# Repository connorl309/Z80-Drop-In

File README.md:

# Z80-Drop-In
Relevant links and information:
- [Instruction Set](https://map.grauw.nl/resources/z80instr.php)
- [Z80 User Manual](https://www.zilog.com/docs/z80/um0080.pdf)
- [Master Reference Website](http://z80.info/)
- [Timing Quirks](https://floooh.github.io/2021/12/06/z80-instruction-timing.html#extra-clock-cycles)

## Summary
This is the Github repository for the senior design capstone project class at the University of Texas at Austin's ECE program (ECE 364/464). Our group is Industry Honors 01 (IH01), a Drop-in CPU Replacement for the Zilog Z80 processor, comprised of six members:

1. [Connor Leu](https://github.com/connorl309) - Team lead, organizer, maintainer, PCB design
2. [April Douglas](https://github.com/MaprilBear) - ALU RTL, processor design
3. [Gage Miller](https://github.com/millergage) - Register file RTL, processor design
4. [Luke Mason](https://github.com/Mega567835) - Control store, microsequencer, FSM design
5. [Nadia Houston](https://github.com/nadiahouston) - Control store, microsequencer, FSM design
6. [Gabriel Moore](https://github.com/K0-p) - Hardware testing, development boards

This project is considered an industry-honors project; as such, we are sponsored and primarily funded by an industry company, [Phoenix Semiconductor](https://www.phoenixsemicorp.com/).

The premise behind our drop-in replacement is to create a cycle-accurate processor core emulator on an FPGA. For our project, under company guidance, we are targeting the Spartan-7 XC7S15. The emulated processor core will sit on a supporting custom PCB, sized to the original form factor (approx. 17mm x 50mm) of the Zilog Z80. This PCB will then assume the position of a Z80 in any Z80 system, mimicking original processor behavior accurately.

The two major components of this project is the processor design and the hardware design. Our processor emulation core is split into datapath design and a control store/microcode FSM. The three major components of the datapath are the ALU, register file, and control logic. The control store and microcode represent our implementation of the original Z80's PLA for instruction decode and processor operation. Our RTL design decisions have been informed by over 40 years of processor execution behavior, the original user manual, and countless online documents written by reverse engineers and hobbyists. (see [Master Reference Website](http://z80.info/))

The hardware design is also split into two primary components: the devhat translation boards, used to level-shift our development boards 3.3V signals to the Z80 5V level and vice versa, and the System-in-Package board, which is the final goal of the project. The SiP board features the Spartan-7 FPGA, control hardware, QSPI flash memory, and other supporting circuitry in the size of the original Z80 package. Our hope is that this final board will be a true drop-in replacement for Z80 processors.

The SiP board can be found in [hardware/sip-board](hardware/sip-board/), and the level shifter board can be found in [hardware/level-shifter/](hardware/level-shifter/). Component files are kind of messy, but both Kicad Projects should all be using RELATIVE paths for custom symbols and footprints.

## Tools
Given the nature of an FPGA-based processor emulator, we opted to use as many industry-standard tools as possible. Our RTL is written in Verilog under the Vivado Design Suite, targeting a Spartan-7 **XC7S15** FPGA for final project completion. We are hoping to acquire physical testing equipment to validate circuit boards. Our hardware is designed using KiCad, as the University does not provide licenses for software such as Altium or Allegro.

## Building and Testing
Vivado's IP for FPGAs has lots of different blocks we can use. One such IP block is the [integrated logic analyzer (ILA)](https://www.xilinx.com/products/intellectual-property/ila.html). Instead of needing more PCBs or fancy test rigs, we can utilize the ILA directly on our development FPGA boards and dump waveforms right back out to the host PC and into the Vivado Waveform viewer. This is our primary method of testing and verification on the development boards (purchased from Numato - the Narvi S7). In addition to the ILA, our devboards also contain FTDI chips that let us communicate over serial to the host computer.
Our goal for devboard testing is to be able to execute any number of sample programs for the Z80, and verify that all control signals are accurate to both the M- and T-cycle level. This will likely take the form of short sample programs for all instructions, and then combined into larger test programs with more complex behavior whose validity will be examined on a results level, not a cycle level.

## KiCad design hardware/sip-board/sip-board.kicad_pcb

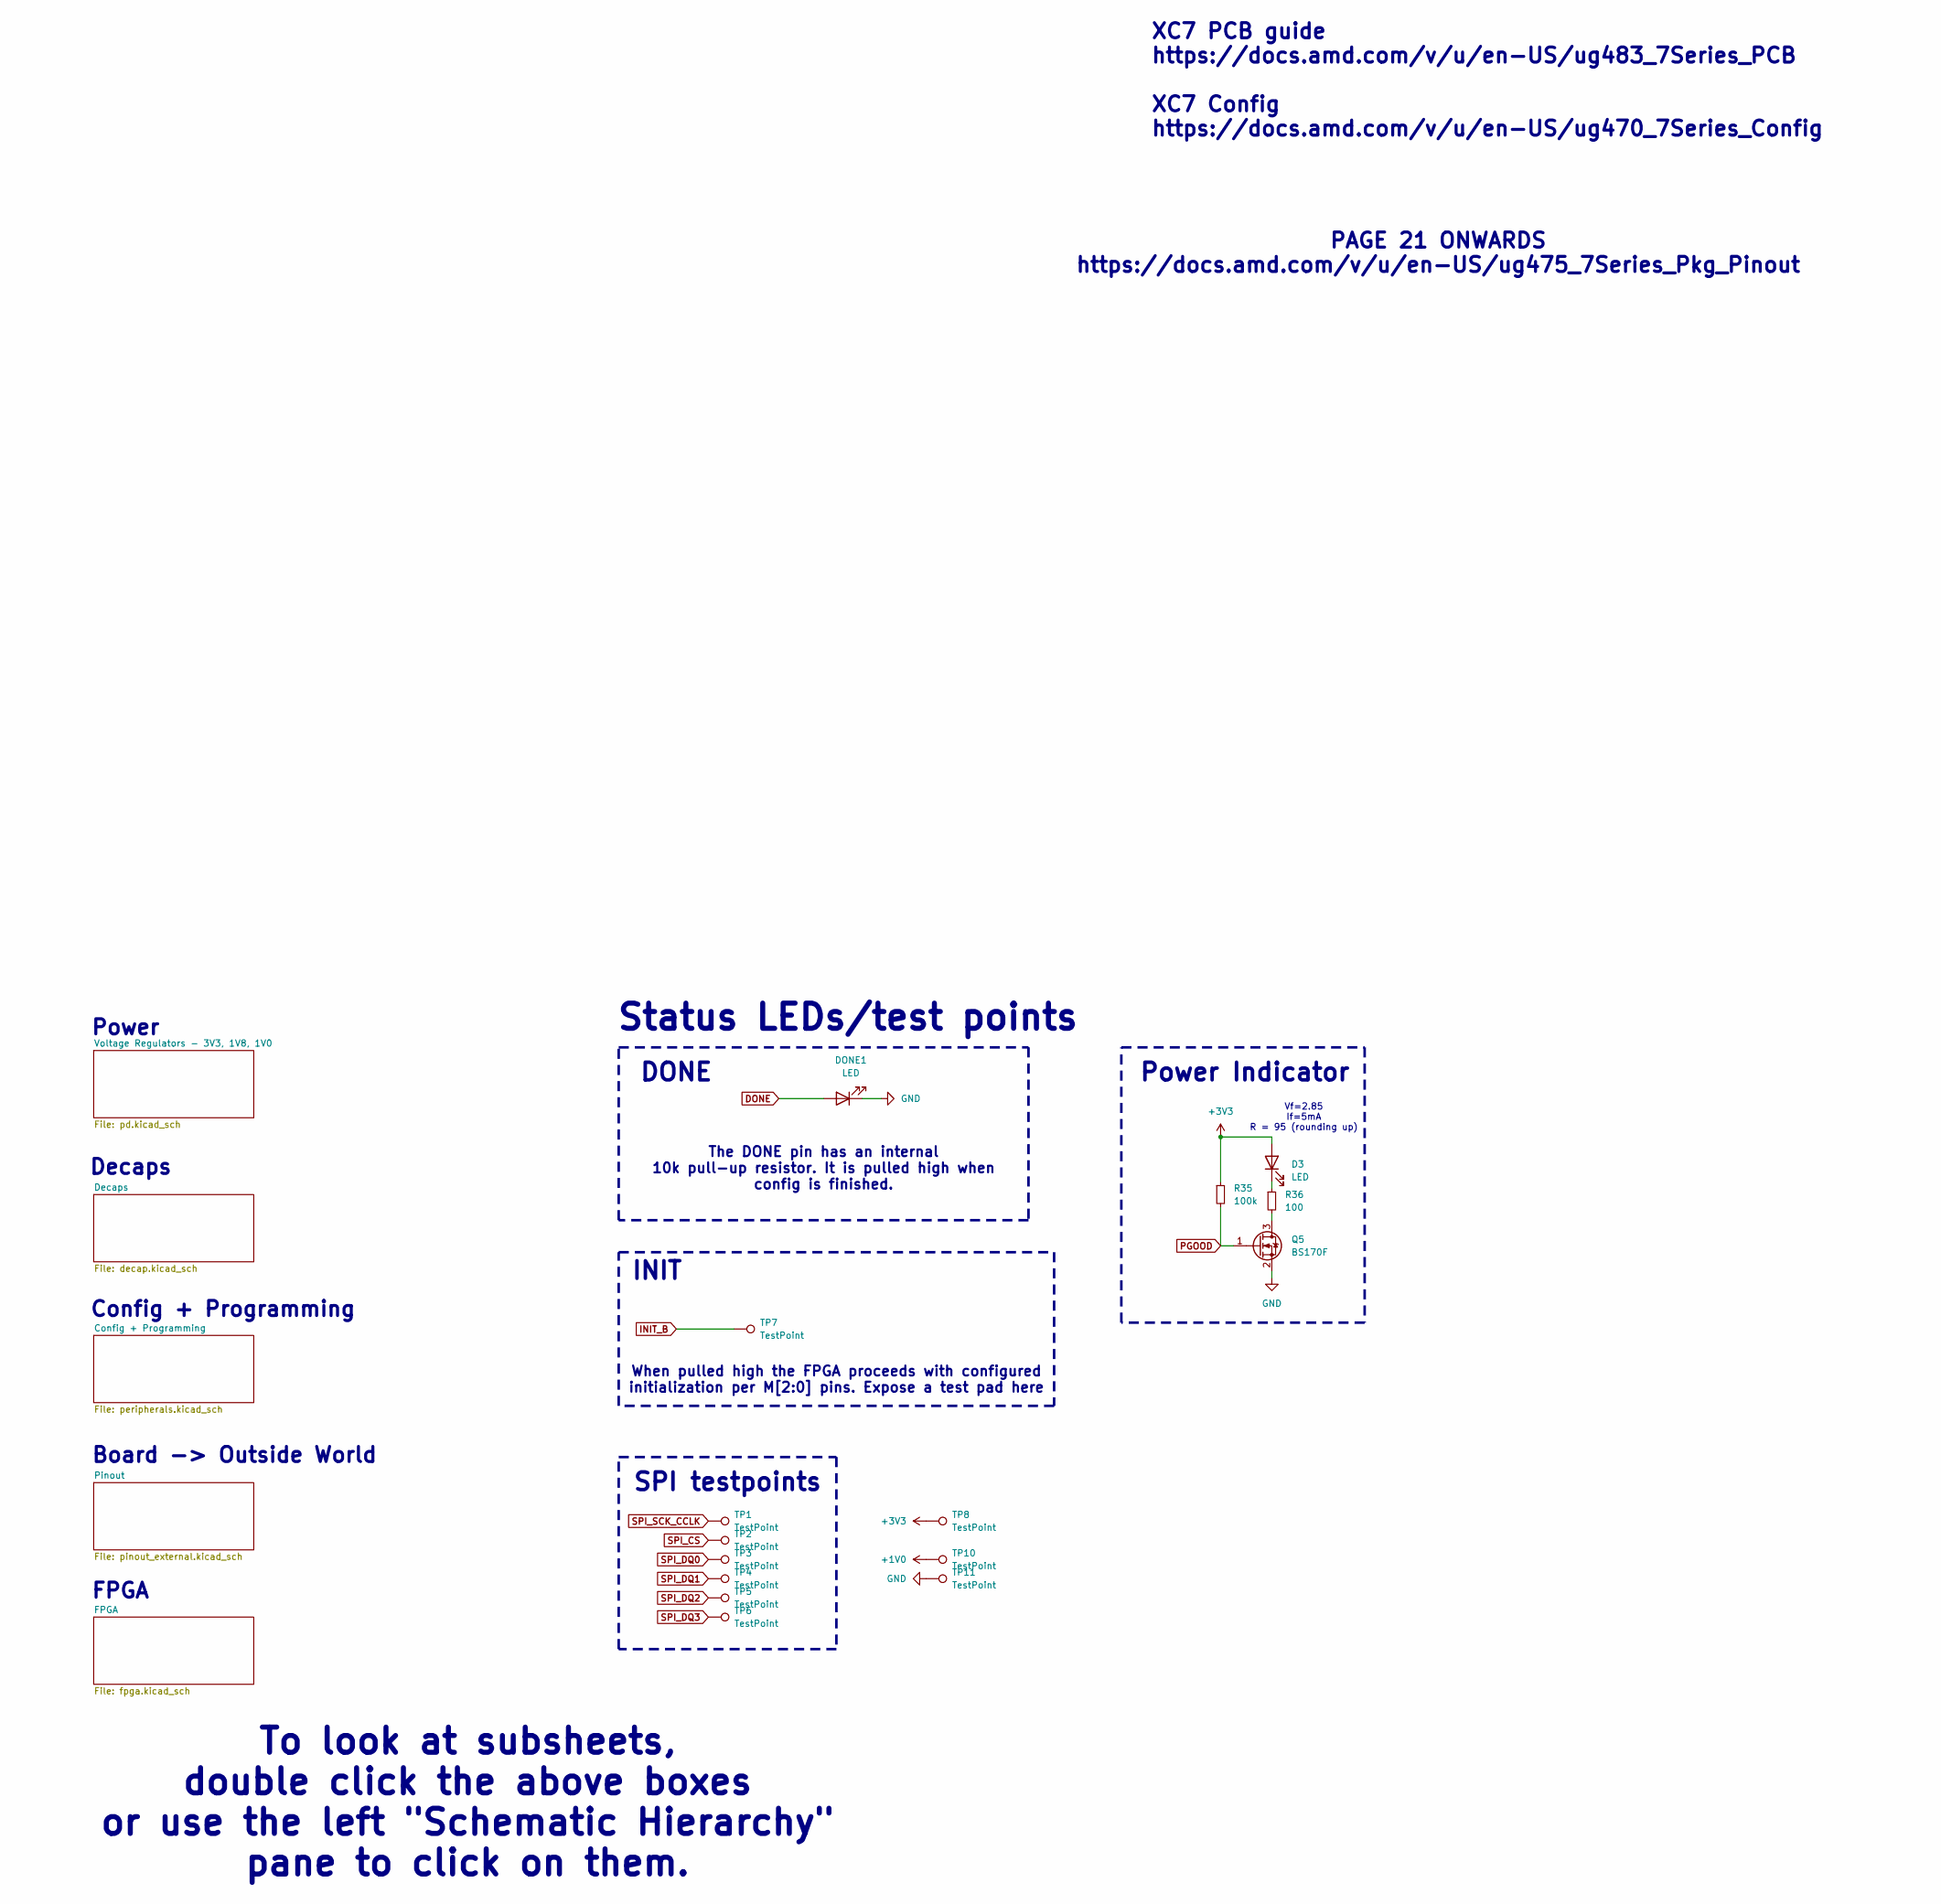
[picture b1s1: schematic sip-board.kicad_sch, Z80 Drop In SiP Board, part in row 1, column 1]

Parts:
D3: LED; LED_0402_1005Metric
DONE1: LED; LED_0402_1005Metric
Q5: BS170F; SOT-23
R35: 100k; R_0201_0603Metric
R36: 100; R_0201_0603Metric
TP1, TP2, TP3, TP4, TP5, TP6, TP7, TP8, TP10, TP11: TestPoint; TestPoint_Pad_1.0x1.0mm

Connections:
+1V0: TP10.1; also elsewhere on the board
+3V3: D3.2 (A), R35.1, TP8.1; also elsewhere on the board
DONE: DONE1.2 (A); also elsewhere on the board
GND: DONE1.1 (K), Q5.2 (S), TP11.1; also elsewhere on the board
INIT_B: TP7.1; also elsewhere on the board
unnamed: D3.1 (K), R36.1
unnamed: Q5.3 (D), R36.2
PGOOD: Q5.1 (G), R35.2; also elsewhere on the board
SPI_CS: TP2.1; also elsewhere on the board
SPI_DQ0: TP3.1; also elsewhere on the board
SPI_DQ1: TP4.1; also elsewhere on the board
SPI_DQ2: TP5.1; also elsewhere on the board
SPI_DQ3: TP6.1; also elsewhere on the board
SPI_SCK_CCLK: TP1.1; also elsewhere on the board

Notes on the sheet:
Power
Status LEDs/test points
FPGA
Decaps
XC7 PCB guide https://docs.amd.com/v/u/en-US/ug483_7Series_PCB XC7 Config https://docs.amd.com/v/u/en-US/ug470_7Series_Config
Board -> Outside World
Power Indicator
PAGE 21 ONWARDS https://docs.amd.com/v/u/en-US/ug475_7Series_Pkg_Pinout
INIT
Config + Programming
https://docs.amd.com/r/en-US/ug1099-bga-device-design-rules/Power-Delivery-to-the-FPGA
When pulled high the FPGA proceeds with configured initialization per M[2:0] pins. Expose a test pad here
DONE
The DONE pin has an internal 10k pull-up resistor. It is pulled high when config is finished.
SPI testpoints
To look at subsheets, double click the above boxes or use the left "Schematic Hierarchy" pane to click on them.
Vf=2.85 If=5mA R = 95 (rounding up)

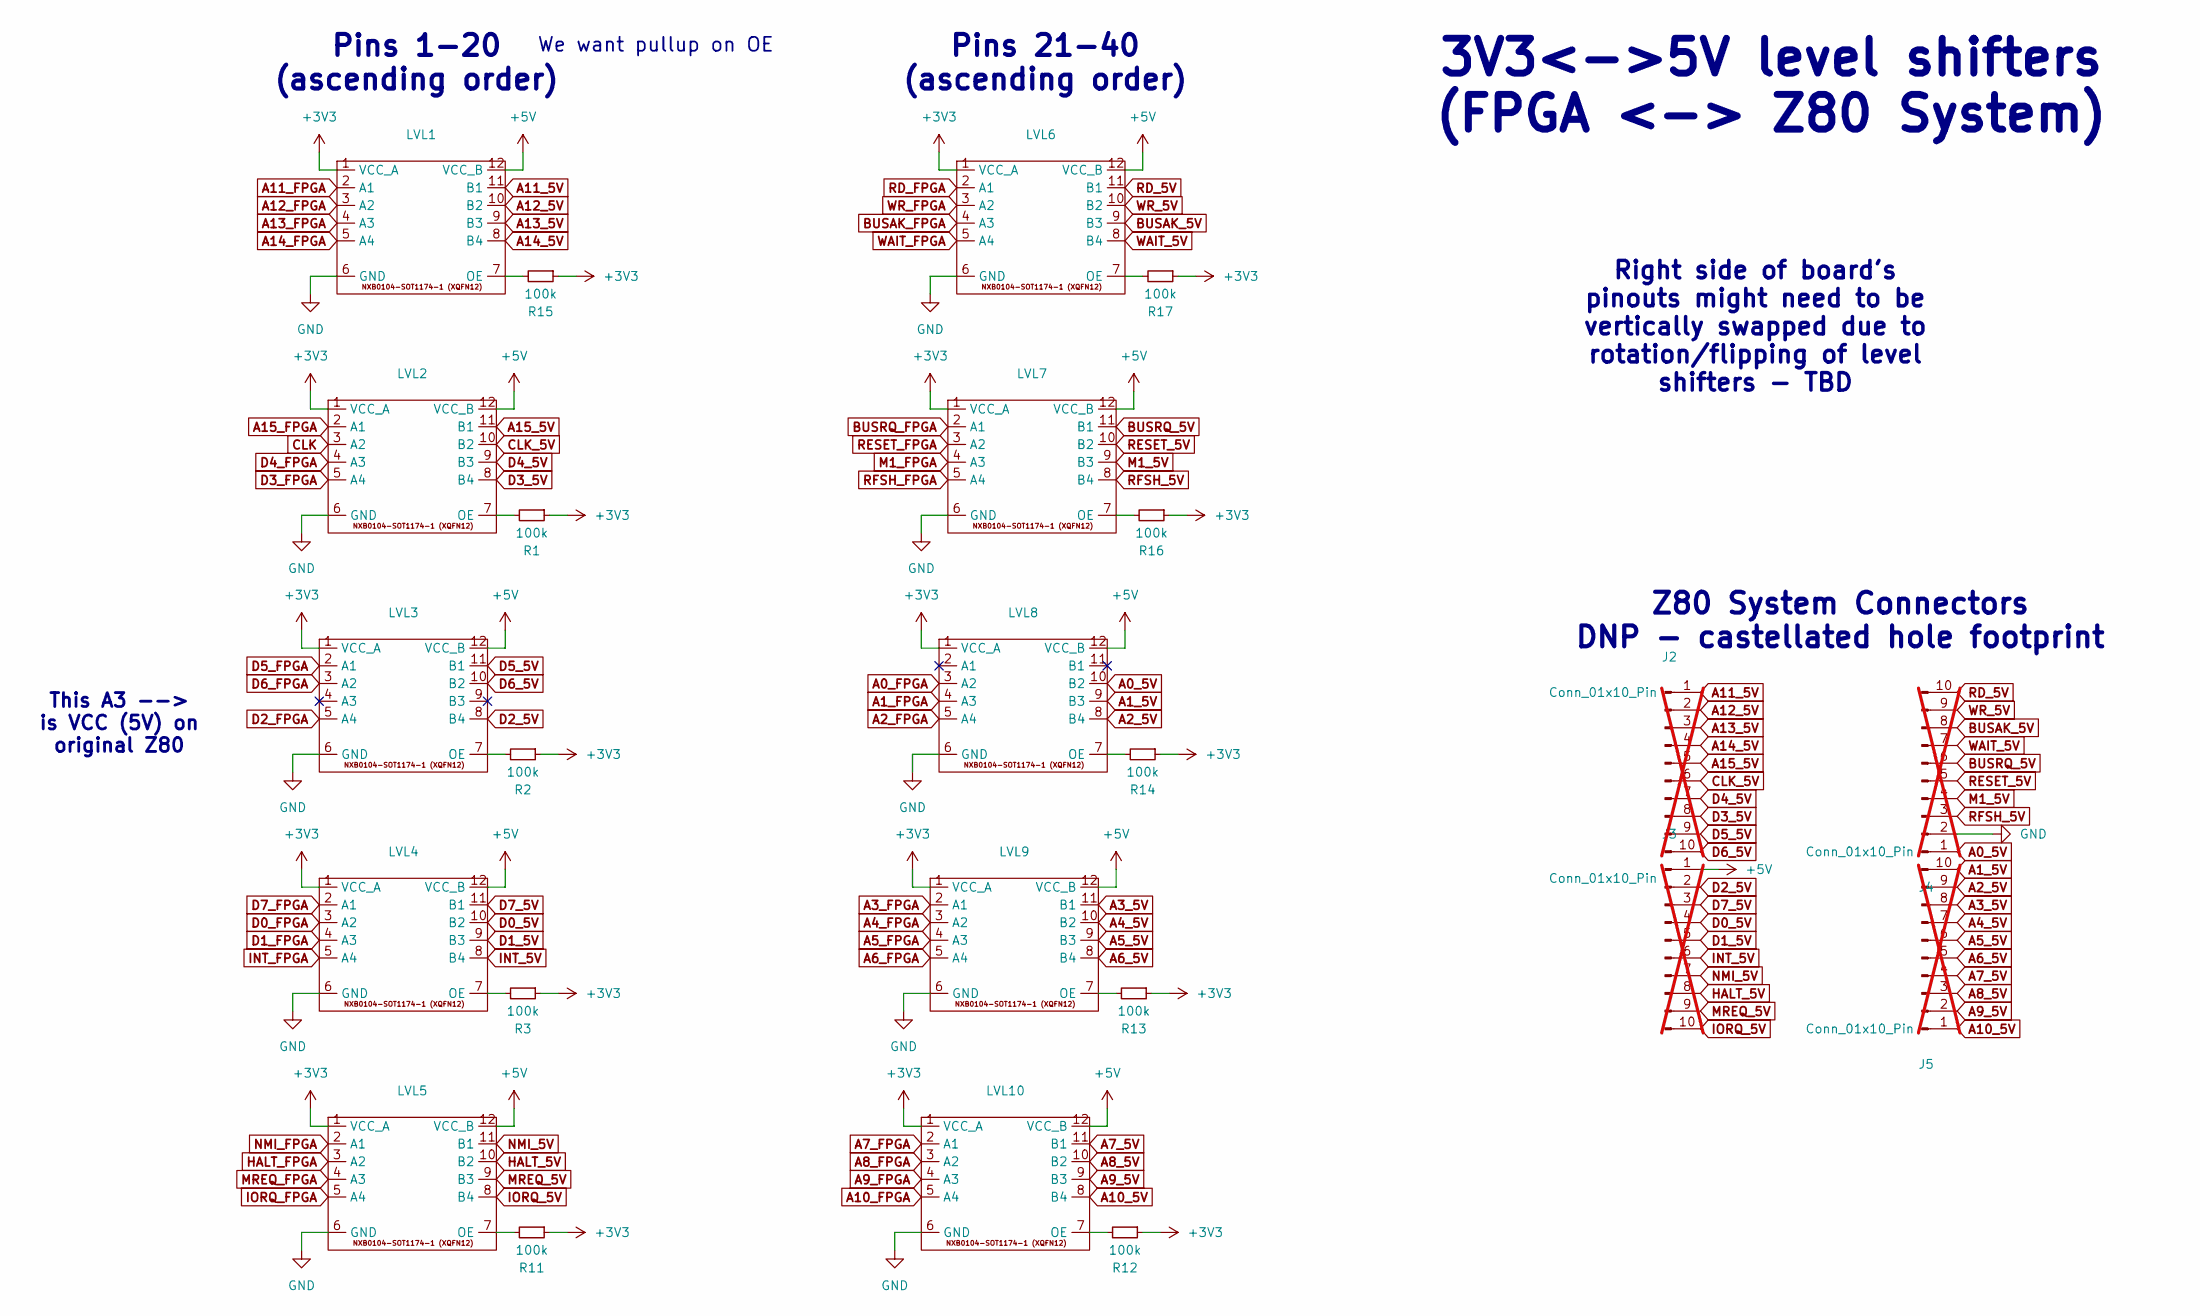
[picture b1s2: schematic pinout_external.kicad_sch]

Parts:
J2, J3, J4, J5: Conn_01x10_Pin; PinHeader_1x10_P2.54mm_Vertical; not fitted
LVL1, LVL2, LVL3, LVL4, LVL5, LVL6, LVL7, LVL8, LVL9, LVL10: NXB0104GU12X; MPN NXB0104GU12X
R1, R2, R3, R11, R12, R13, R14, R15, R16, R17: 100k; R_0201_0603Metric

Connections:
+3V3: LVL1.1 (VCC_A), LVL2.1 (VCC_A), LVL3.1 (VCC_A), LVL4.1 (VCC_A), LVL5.1 (VCC_A), LVL6.1 (VCC_A), LVL7.1 (VCC_A), LVL8.1 (VCC_A), LVL9.1 (VCC_A), LVL10.1 (VCC_A), R1.1, R2.1, R3.1, R11.1, R12.1, R13.1, R14.1, R15.1, R16.1, R17.1; also elsewhere on the board
+5V: J3.1, LVL1.12 (VCC_B), LVL2.12 (VCC_B), LVL3.12 (VCC_B), LVL4.12 (VCC_B), LVL5.12 (VCC_B), LVL6.12 (VCC_B), LVL7.12 (VCC_B), LVL8.12 (VCC_B), LVL9.12 (VCC_B), LVL10.12 (VCC_B); also elsewhere on the board
A0_5V: J4.1, LVL8.10 (B2)
A0_FPGA: LVL8.3 (A2); also elsewhere on the board
A1_5V: J5.10, LVL8.9 (B3)
A1_FPGA: LVL8.4 (A3); also elsewhere on the board
A2_5V: J5.9, LVL8.8 (B4)
A2_FPGA: LVL8.5 (A4); also elsewhere on the board
A3_5V: J5.8, LVL9.11 (B1)
A3_FPGA: LVL9.2 (A1); also elsewhere on the board
A4_5V: J5.7, LVL9.10 (B2)
A4_FPGA: LVL9.3 (A2); also elsewhere on the board
A5_5V: J5.6, LVL9.9 (B3)
A5_FPGA: LVL9.4 (A3); also elsewhere on the board
A6_5V: J5.5, LVL9.8 (B4)
A6_FPGA: LVL9.5 (A4); also elsewhere on the board
A7_5V: J5.4, LVL10.11 (B1)
A7_FPGA: LVL10.2 (A1); also elsewhere on the board
A8_5V: J5.3, LVL10.10 (B2)
A8_FPGA: LVL10.3 (A2); also elsewhere on the board
A9_5V: J5.2, LVL10.9 (B3)
A9_FPGA: LVL10.4 (A3); also elsewhere on the board
A10_5V: J5.1, LVL10.8 (B4)
A10_FPGA: LVL10.5 (A4); also elsewhere on the board
A11_5V: J2.1, LVL1.11 (B1)
A11_FPGA: LVL1.2 (A1); also elsewhere on the board
A12_5V: J2.2, LVL1.10 (B2)
A12_FPGA: LVL1.3 (A2); also elsewhere on the board
A13_5V: J2.3, LVL1.9 (B3)
A13_FPGA: LVL1.4 (A3); also elsewhere on the board
A14_5V: J2.4, LVL1.8 (B4)
A14_FPGA: LVL1.5 (A4); also elsewhere on the board
A15_5V: J2.5, LVL2.11 (B1)
A15_FPGA: LVL2.2 (A1); also elsewhere on the board
BUSAK_5V: J4.8, LVL6.9 (B3)
BUSAK_FPGA: LVL6.4 (A3); also elsewhere on the board
BUSRQ_5V: J4.6, LVL7.11 (B1)
BUSRQ_FPGA: LVL7.2 (A1); also elsewhere on the board
CLK: LVL2.3 (A2); also elsewhere on the board
CLK_5V: J2.6, LVL2.10 (B2)
D0_5V: J3.4, LVL4.10 (B2)
D0_FPGA: LVL4.3 (A2); also elsewhere on the board
D1_5V: J3.5, LVL4.9 (B3)
D1_FPGA: LVL4.4 (A3); also elsewhere on the board
D2_5V: J3.2, LVL3.8 (B4)
D2_FPGA: LVL3.5 (A4); also elsewhere on the board
D3_5V: J2.8, LVL2.8 (B4)
D3_FPGA: LVL2.5 (A4); also elsewhere on the board
D4_5V: J2.7, LVL2.9 (B3)
D4_FPGA: LVL2.4 (A3); also elsewhere on the board
D5_5V: J2.9, LVL3.11 (B1)
D5_FPGA: LVL3.2 (A1); also elsewhere on the board
D6_5V: J2.10, LVL3.10 (B2)
D6_FPGA: LVL3.3 (A2); also elsewhere on the board
D7_5V: J3.3, LVL4.11 (B1)
D7_FPGA: LVL4.2 (A1); also elsewhere on the board
GND: J4.2, LVL1.6 (GND), LVL2.6 (GND), LVL3.6 (GND), LVL4.6 (GND), LVL5.6 (GND), LVL6.6 (GND), LVL7.6 (GND), LVL8.6 (GND), LVL9.6 (GND), LVL10.6 (GND); also elsewhere on the board
HALT_5V: J3.8, LVL5.10 (B2)
HALT_FPGA: LVL5.3 (A2); also elsewhere on the board
INT_5V: J3.6, LVL4.8 (B4)
INT_FPGA: LVL4.5 (A4); also elsewhere on the board
IORQ_5V: J3.10, LVL5.8 (B4)
IORQ_FPGA: LVL5.5 (A4); also elsewhere on the board
M1_5V: J4.4, LVL7.9 (B3)
M1_FPGA: LVL7.4 (A3); also elsewhere on the board
MREQ_5V: J3.9, LVL5.9 (B3)
MREQ_FPGA: LVL5.4 (A3); also elsewhere on the board
NMI_5V: J3.7, LVL5.11 (B1)
NMI_FPGA: LVL5.2 (A1); also elsewhere on the board
unnamed: LVL1.7 (OE), R15.2
unnamed: LVL2.7 (OE), R1.2
unnamed: LVL3.7 (OE), R2.2
unnamed: LVL4.7 (OE), R3.2
unnamed: LVL5.7 (OE), R11.2
unnamed: LVL6.7 (OE), R17.2
unnamed: LVL7.7 (OE), R16.2
unnamed: LVL8.7 (OE), R14.2
unnamed: LVL9.7 (OE), R13.2
unnamed: LVL10.7 (OE), R12.2
RD_5V: J4.10, LVL6.11 (B1)
RD_FPGA: LVL6.2 (A1); also elsewhere on the board
RESET_5V: J4.5, LVL7.10 (B2)
RESET_FPGA: LVL7.3 (A2); also elsewhere on the board
RFSH_5V: J4.3, LVL7.8 (B4)
RFSH_FPGA: LVL7.5 (A4); also elsewhere on the board
WAIT_5V: J4.7, LVL6.8 (B4)
WAIT_FPGA: LVL6.5 (A4); also elsewhere on the board
WR_5V: J4.9, LVL6.10 (B2)
WR_FPGA: LVL6.3 (A2); also elsewhere on the board

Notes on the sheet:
3V3<->5V level shifters (FPGA <-> Z80 System)
Z80 System Connectors DNP - castellated hole footprint
This A3 --> is VCC (5V) on original Z80
We want pullup on OE
Right side of board's pinouts might need to be vertically swapped due to rotation/flipping of level shifters - TBD
Pins 21-40 (ascending order)
Pins 1-20 (ascending order)

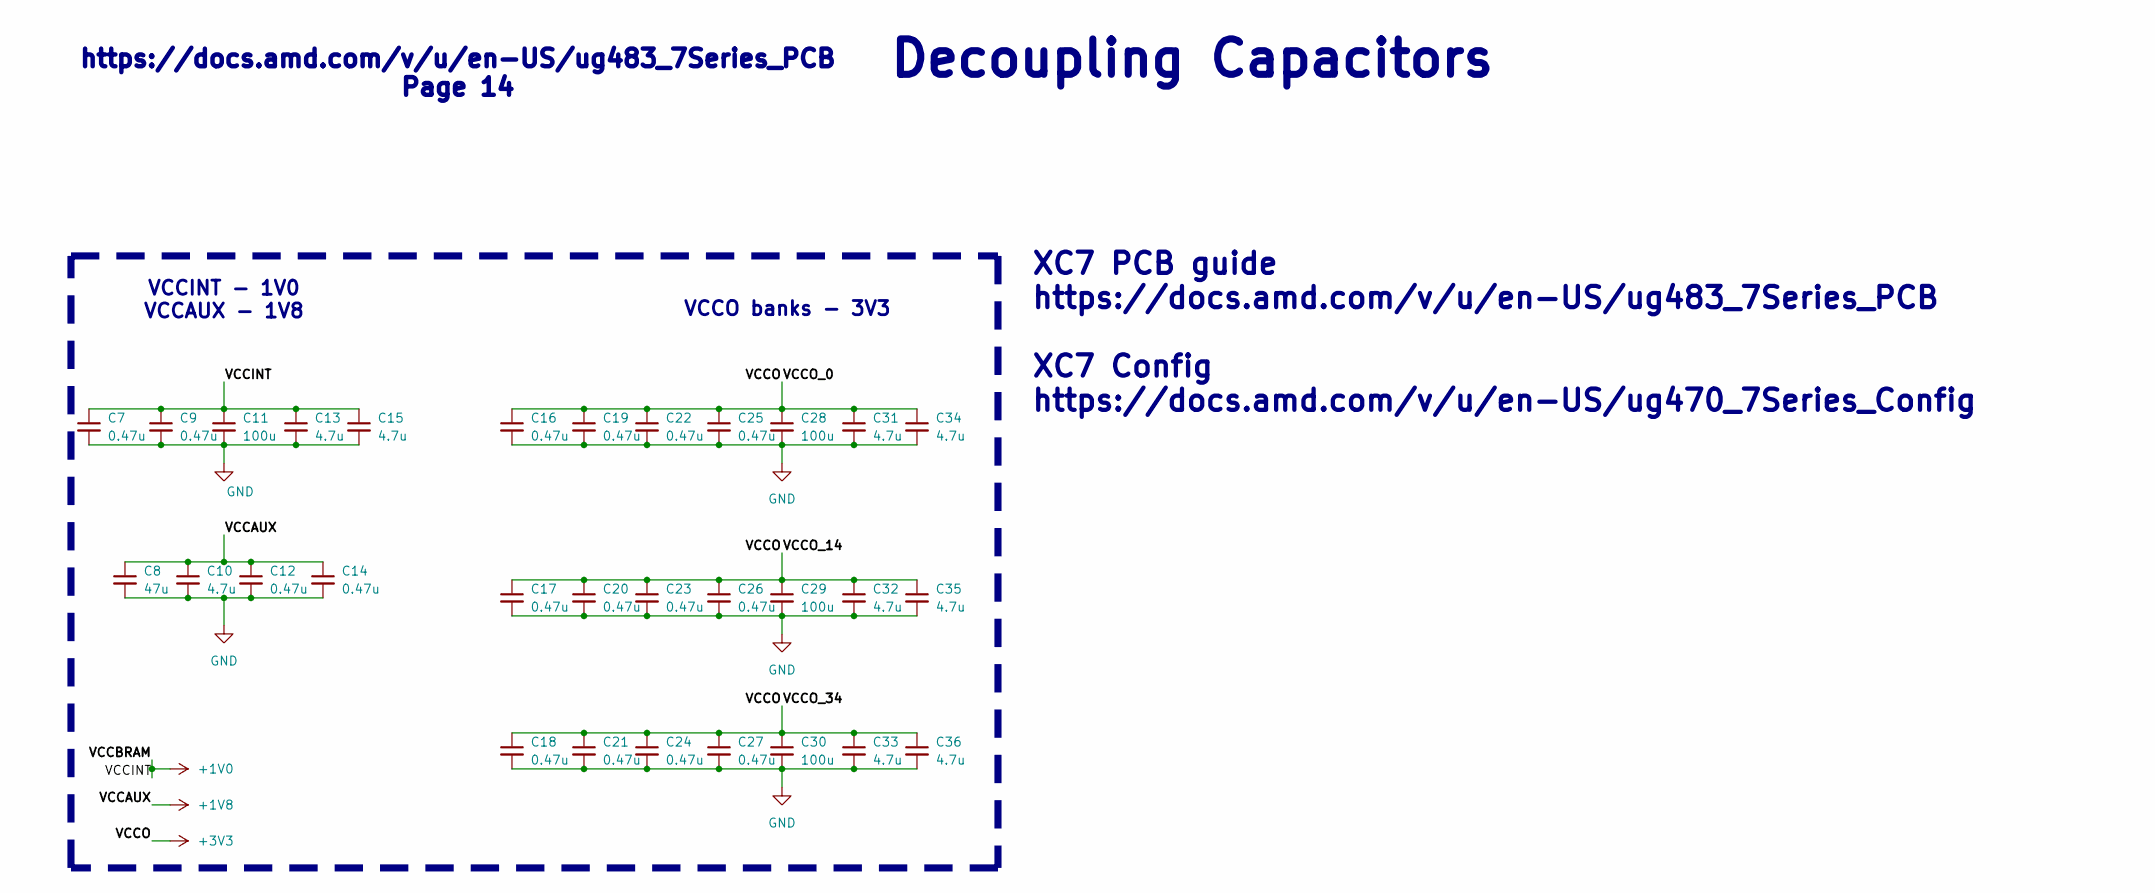
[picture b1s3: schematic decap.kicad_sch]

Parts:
C7, C9, C12, C14, C16, C17, C18, C19, C20, C21, C22, C23, C24, C25, C26, C27: 0.47u; C_0201_0603Metric
C8: 47u; C_0603_1608Metric
C10, C13, C15, C31, C32, C33, C34, C35, C36: 4.7u; C_0402_1005Metric
C11, C28, C29, C30: 100u; C_0603_1608Metric

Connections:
+1V0: C7.1, C9.1, C11.1, C13.1, C15.1; also elsewhere on the board
+1V8: C8.1, C10.1, C12.1, C14.1; also elsewhere on the board
+3V3: C16.1, C17.1, C18.1, C19.1, C20.1, C21.1, C22.1, C23.1, C24.1, C25.1, C26.1, C27.1, C28.1, C29.1, C30.1, C31.1, C32.1, C33.1, C34.1, C35.1, C36.1; also elsewhere on the board
GND: C7.2, C8.2, C9.2, C10.2, C11.2, C12.2, C13.2, C14.2, C15.2, C16.2, C17.2, C18.2, C19.2, C20.2, C21.2, C22.2, C23.2, C24.2, C25.2, C26.2, C27.2, C28.2, C29.2, C30.2, C31.2, C32.2, C33.2, C34.2, C35.2, C36.2; also elsewhere on the board

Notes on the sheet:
Decoupling Capacitors
XC7 PCB guide https://docs.amd.com/v/u/en-US/ug483_7Series_PCB XC7 Config https://docs.amd.com/v/u/en-US/ug470_7Series_Config
VCCO banks - 3V3
https://docs.amd.com/v/u/en-US/ug483_7Series_PCB Page 14
VCCINT - 1V0 VCCAUX - 1V8

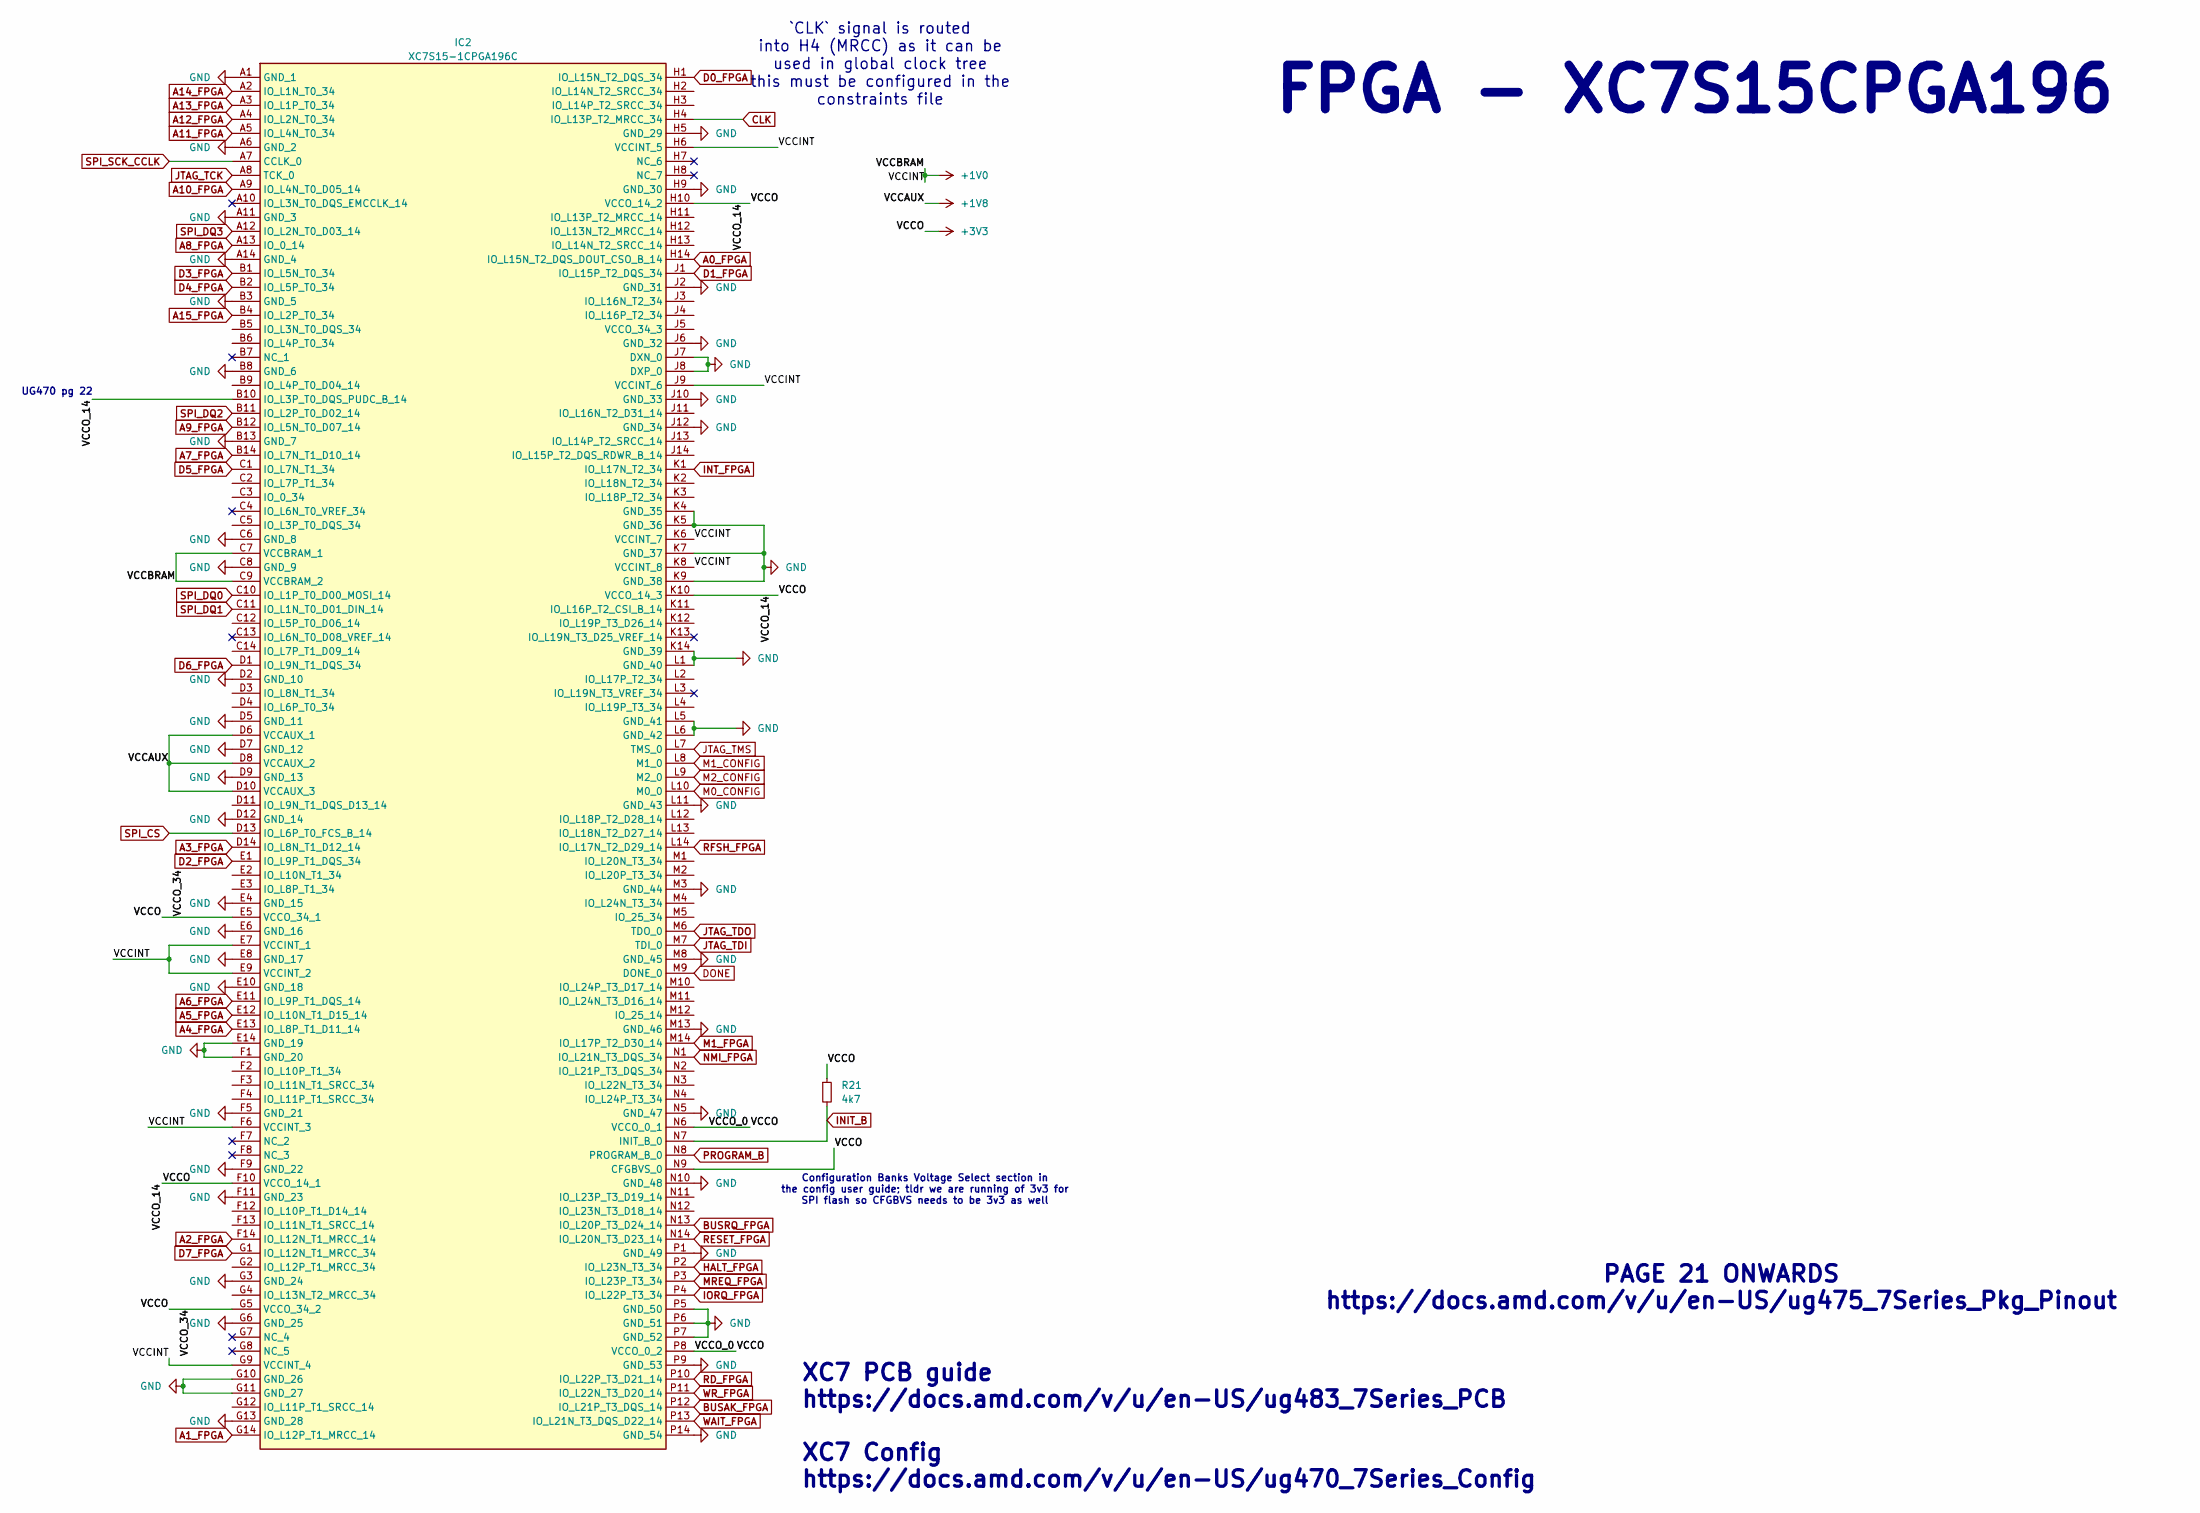
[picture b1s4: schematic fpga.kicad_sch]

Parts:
IC2: XC7S15-1CPGA196C; BGA196C50P14X14_800X800X110; Mouser Part Number 217-XC7S15-1CPGA196C
R21: 4k7; R_0201_0603Metric

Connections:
+1V0: IC2.C7 (VCCBRAM_1), IC2.C9 (VCCBRAM_2), IC2.E7 (VCCINT_1), IC2.E9 (VCCINT_2), IC2.F6 (VCCINT_3), IC2.G9 (VCCINT_4), IC2.H6 (VCCINT_5), IC2.J9 (VCCINT_6), IC2.K6 (VCCINT_7), IC2.K8 (VCCINT_8); also elsewhere on the board
+1V8: IC2.D6 (VCCAUX_1), IC2.D8 (VCCAUX_2), IC2.D10 (VCCAUX_3); also elsewhere on the board
+3V3: IC2.B10 (IO_L3P_T0_DQS_PUDC_B_14), IC2.E5 (VCCO_34_1), IC2.F10 (VCCO_14_1), IC2.G5 (VCCO_34_2), IC2.H10 (VCCO_14_2), IC2.K10 (VCCO_14_3), IC2.N6 (VCCO_0_1), IC2.N9 (CFGBVS_0), IC2.P8 (VCCO_0_2), R21.1; also elsewhere on the board
A0_FPGA: IC2.H14 (IO_L15N_T2_DQS_DOUT_CSO_B_14); also elsewhere on the board
A1_FPGA: IC2.G14 (IO_L12P_T1_MRCC_14); also elsewhere on the board
A2_FPGA: IC2.F14 (IO_L12N_T1_MRCC_14); also elsewhere on the board
A3_FPGA: IC2.D14 (IO_L8N_T1_D12_14); also elsewhere on the board
A4_FPGA: IC2.E13 (IO_L8P_T1_D11_14); also elsewhere on the board
A5_FPGA: IC2.E12 (IO_L10N_T1_D15_14); also elsewhere on the board
A6_FPGA: IC2.E11 (IO_L9P_T1_DQS_14); also elsewhere on the board
A7_FPGA: IC2.B14 (IO_L7N_T1_D10_14); also elsewhere on the board
A8_FPGA: IC2.A13 (IO_0_14); also elsewhere on the board
A9_FPGA: IC2.B12 (IO_L5N_T0_D07_14); also elsewhere on the board
A10_FPGA: IC2.A9 (IO_L4N_T0_D05_14); also elsewhere on the board
A11_FPGA: IC2.A5 (IO_L4N_T0_34); also elsewhere on the board
A12_FPGA: IC2.A4 (IO_L2N_T0_34); also elsewhere on the board
A13_FPGA: IC2.A3 (IO_L1P_T0_34); also elsewhere on the board
A14_FPGA: IC2.A2 (IO_L1N_T0_34); also elsewhere on the board
A15_FPGA: IC2.B4 (IO_L2P_T0_34); also elsewhere on the board
BUSAK_FPGA: IC2.P12 (IO_L21P_T3_DQS_14); also elsewhere on the board
BUSRQ_FPGA: IC2.N13 (IO_L20P_T3_D24_14); also elsewhere on the board
CLK: IC2.H4 (IO_L13P_T2_MRCC_34); also elsewhere on the board
D0_FPGA: IC2.H1 (IO_L15N_T2_DQS_34); also elsewhere on the board
D1_FPGA: IC2.J1 (IO_L15P_T2_DQS_34); also elsewhere on the board
D2_FPGA: IC2.E1 (IO_L9P_T1_DQS_34); also elsewhere on the board
D3_FPGA: IC2.B1 (IO_L5N_T0_34); also elsewhere on the board
D4_FPGA: IC2.B2 (IO_L5P_T0_34); also elsewhere on the board
D5_FPGA: IC2.C1 (IO_L7N_T1_34); also elsewhere on the board
D6_FPGA: IC2.D1 (IO_L9N_T1_DQS_34); also elsewhere on the board
D7_FPGA: IC2.G1 (IO_L12N_T1_MRCC_34); also elsewhere on the board
DONE: IC2.M9 (DONE_0); also elsewhere on the board
GND: IC2.A1 (GND_1), IC2.A6 (GND_2), IC2.A11 (GND_3), IC2.A14 (GND_4), IC2.B3 (GND_5), IC2.B8 (GND_6), IC2.B13 (GND_7), IC2.C6 (GND_8), IC2.C8 (GND_9), IC2.D2 (GND_10), IC2.D5 (GND_11), IC2.D7 (GND_12), IC2.D9 (GND_13), IC2.D12 (GND_14), IC2.E4 (GND_15), IC2.E6 (GND_16), IC2.E8 (GND_17), IC2.E10 (GND_18), IC2.E14 (GND_19), IC2.F1 (GND_20), IC2.F5 (GND_21), IC2.F9 (GND_22), IC2.F11 (GND_23), IC2.G3 (GND_24), IC2.G6 (GND_25), IC2.G10 (GND_26), IC2.G11 (GND_27), IC2.G13 (GND_28), IC2.H5 (GND_29), IC2.H9 (GND_30), IC2.J2 (GND_31), IC2.J6 (GND_32), IC2.J7 (DXN_0), IC2.J8 (DXP_0), IC2.J10 (GND_33), IC2.J12 (GND_34), IC2.K4 (GND_35), IC2.K5 (GND_36), IC2.K7 (GND_37), IC2.K9 (GND_38), IC2.K14 (GND_39), IC2.L1 (GND_40), IC2.L5 (GND_41), IC2.L6 (GND_42), IC2.L11 (GND_43), IC2.M3 (GND_44), IC2.M8 (GND_45), IC2.M13 (GND_46), IC2.N5 (GND_47), IC2.N10 (GND_48), IC2.P1 (GND_49), IC2.P5 (GND_50), IC2.P6 (GND_51), IC2.P7 (GND_52), IC2.P9 (GND_53), IC2.P14 (GND_54); also elsewhere on the board
HALT_FPGA: IC2.P2 (IO_L23N_T3_34); also elsewhere on the board
INIT_B: IC2.N7 (INIT_B_0), R21.2; also elsewhere on the board
INT_FPGA: IC2.K1 (IO_L17N_T2_34); also elsewhere on the board
IORQ_FPGA: IC2.P4 (IO_L22P_T3_34); also elsewhere on the board
JTAG_TCK: IC2.A8 (TCK_0); also elsewhere on the board
JTAG_TDI: IC2.M7 (TDI_0); also elsewhere on the board
JTAG_TDO: IC2.M6 (TDO_0); also elsewhere on the board
JTAG_TMS: IC2.L7 (TMS_0); also elsewhere on the board
M0_CONFIG: IC2.L10 (M0_0); also elsewhere on the board
M1_CONFIG: IC2.L8 (M1_0); also elsewhere on the board
M1_FPGA: IC2.M14 (IO_L17P_T2_D30_14); also elsewhere on the board
M2_CONFIG: IC2.L9 (M2_0); also elsewhere on the board
MREQ_FPGA: IC2.P3 (IO_L23P_T3_34); also elsewhere on the board
NMI_FPGA: IC2.N1 (IO_L21N_T3_DQS_34); also elsewhere on the board
PROGRAM_B: IC2.N8 (PROGRAM_B_0); also elsewhere on the board
RD_FPGA: IC2.P10 (IO_L22P_T3_D21_14); also elsewhere on the board
RESET_FPGA: IC2.N14 (IO_L20N_T3_D23_14); also elsewhere on the board
RFSH_FPGA: IC2.L14 (IO_L17N_T2_D29_14); also elsewhere on the board
SPI_CS: IC2.D13 (IO_L6P_T0_FCS_B_14); also elsewhere on the board
SPI_DQ0: IC2.C10 (IO_L1P_T0_D00_MOSI_14); also elsewhere on the board
SPI_DQ1: IC2.C11 (IO_L1N_T0_D01_DIN_14); also elsewhere on the board
SPI_DQ2: IC2.B11 (IO_L2P_T0_D02_14); also elsewhere on the board
SPI_DQ3: IC2.A12 (IO_L2N_T0_D03_14); also elsewhere on the board
SPI_SCK_CCLK: IC2.A7 (CCLK_0); also elsewhere on the board
WAIT_FPGA: IC2.P13 (IO_L21N_T3_DQS_D22_14); also elsewhere on the board
WR_FPGA: IC2.P11 (IO_L22N_T3_D20_14); also elsewhere on the board

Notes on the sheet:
UG470 pg 22
XC7 PCB guide https://docs.amd.com/v/u/en-US/ug483_7Series_PCB XC7 Config https://docs.amd.com/v/u/en-US/ug470_7Series_Config
Configuration Banks Voltage Select section in the config user guide; tldr we are running of 3v3 for SPI flash so CFGBVS needs to be 3v3 as well
PAGE 21 ONWARDS https://docs.amd.com/v/u/en-US/ug475_7Series_Pkg_Pinout
`CLK` signal is routed into H4 (MRCC) as it can be used in global clock tree this must be configured in the constraints file
FPGA - XC7S15CPGA196
